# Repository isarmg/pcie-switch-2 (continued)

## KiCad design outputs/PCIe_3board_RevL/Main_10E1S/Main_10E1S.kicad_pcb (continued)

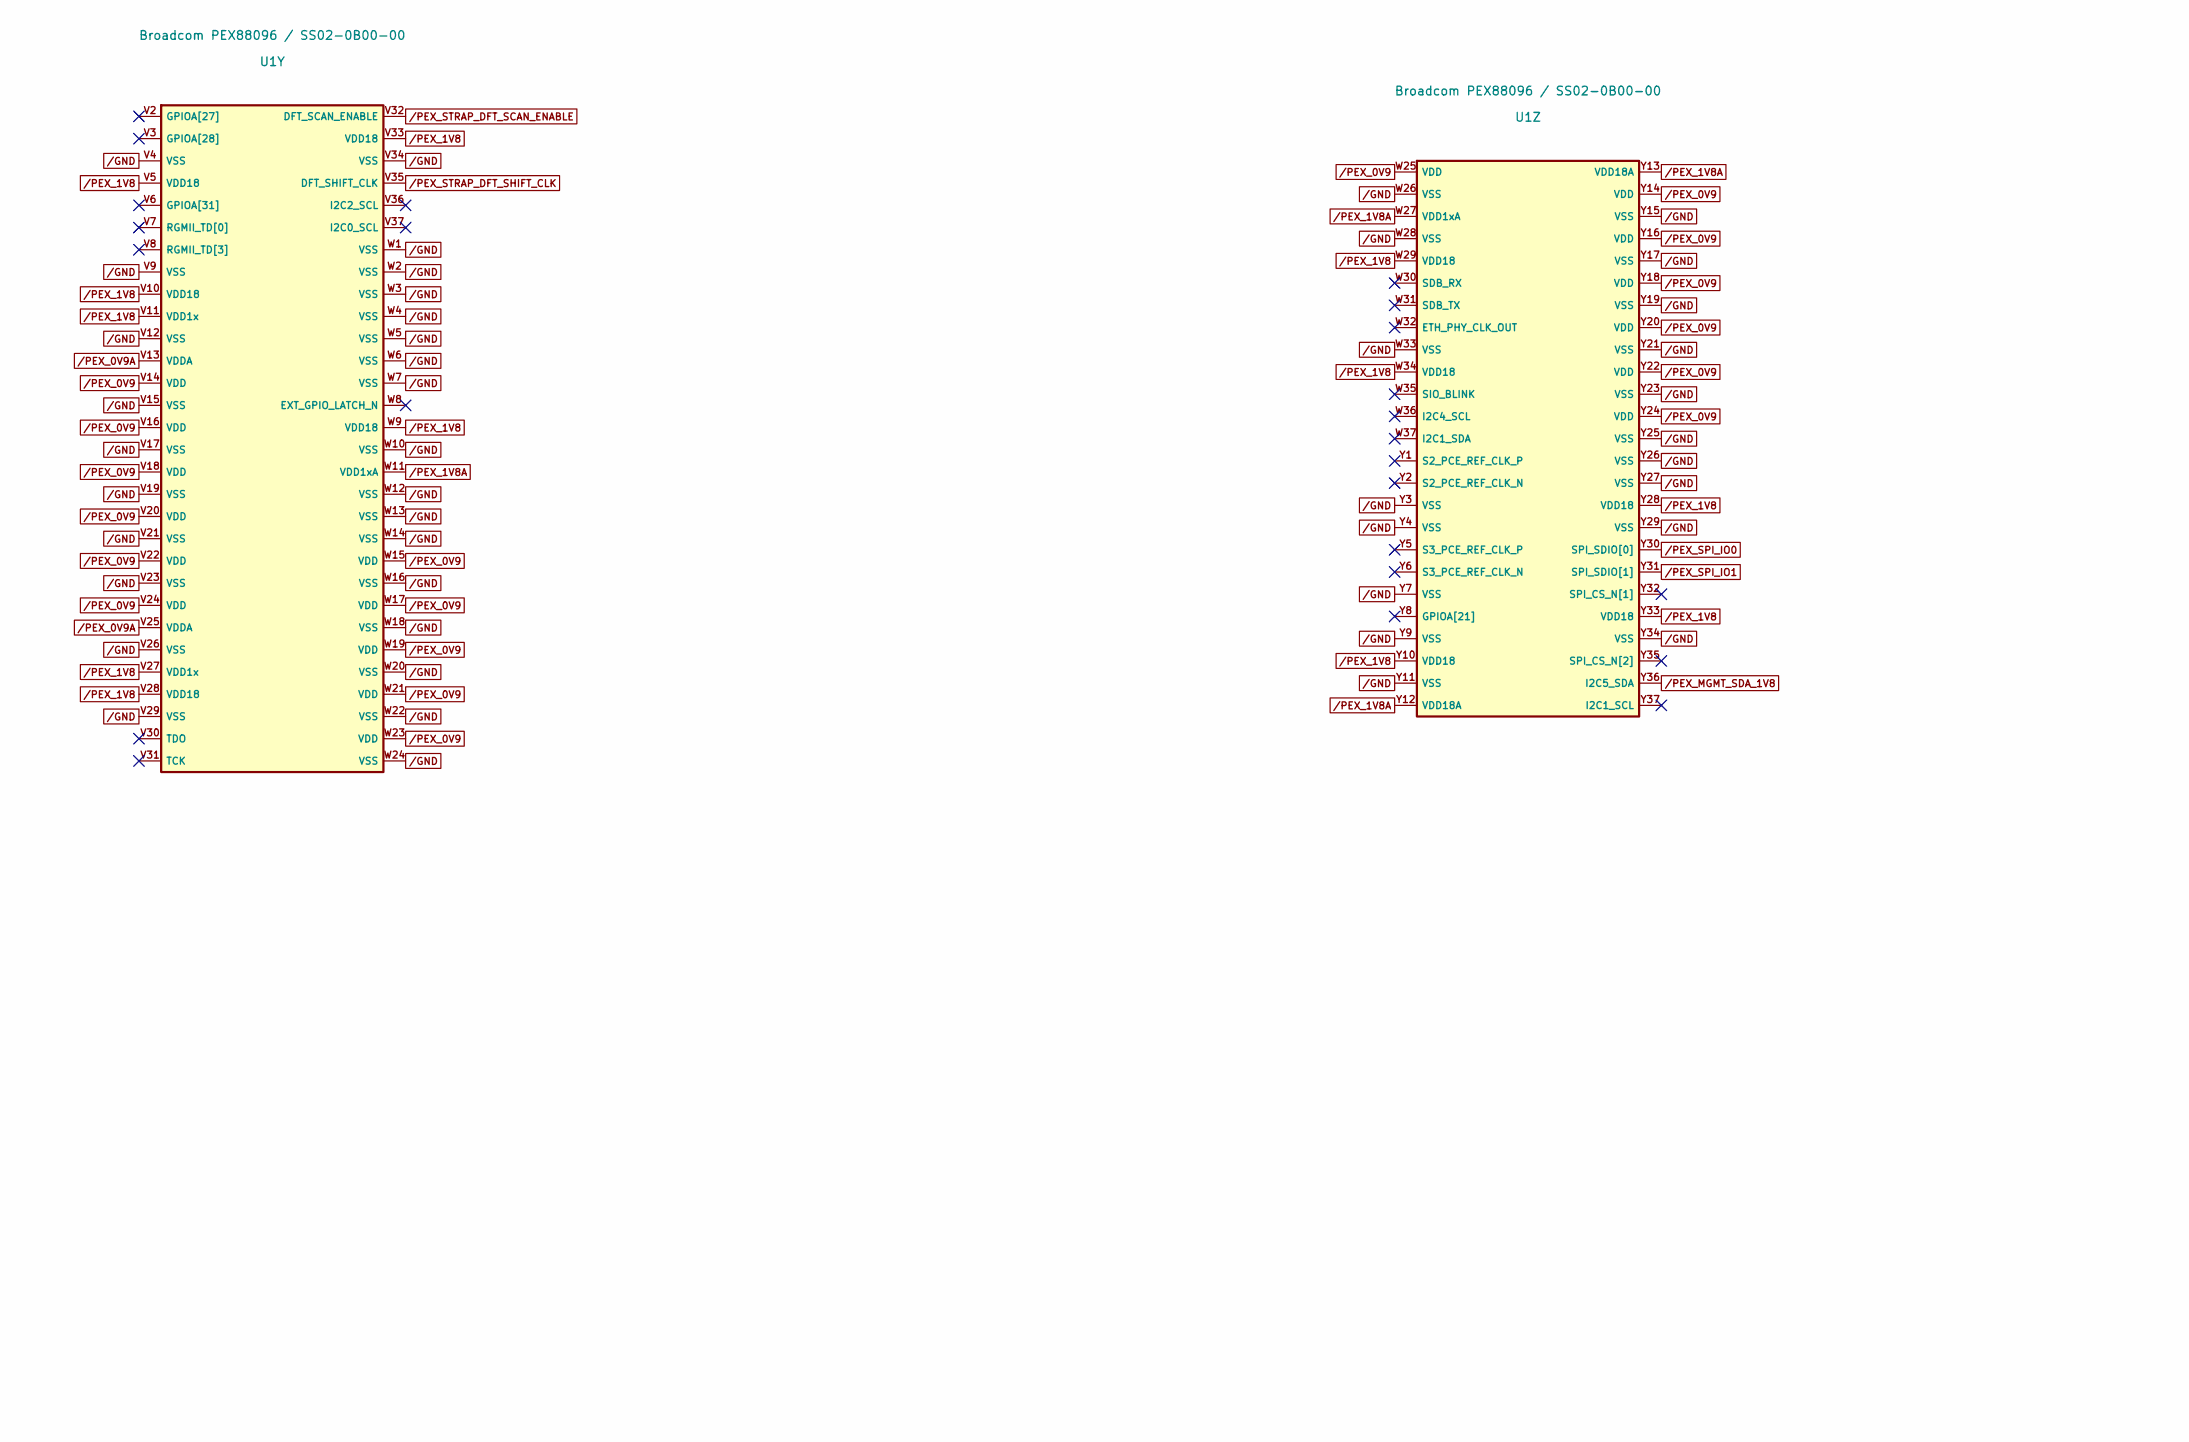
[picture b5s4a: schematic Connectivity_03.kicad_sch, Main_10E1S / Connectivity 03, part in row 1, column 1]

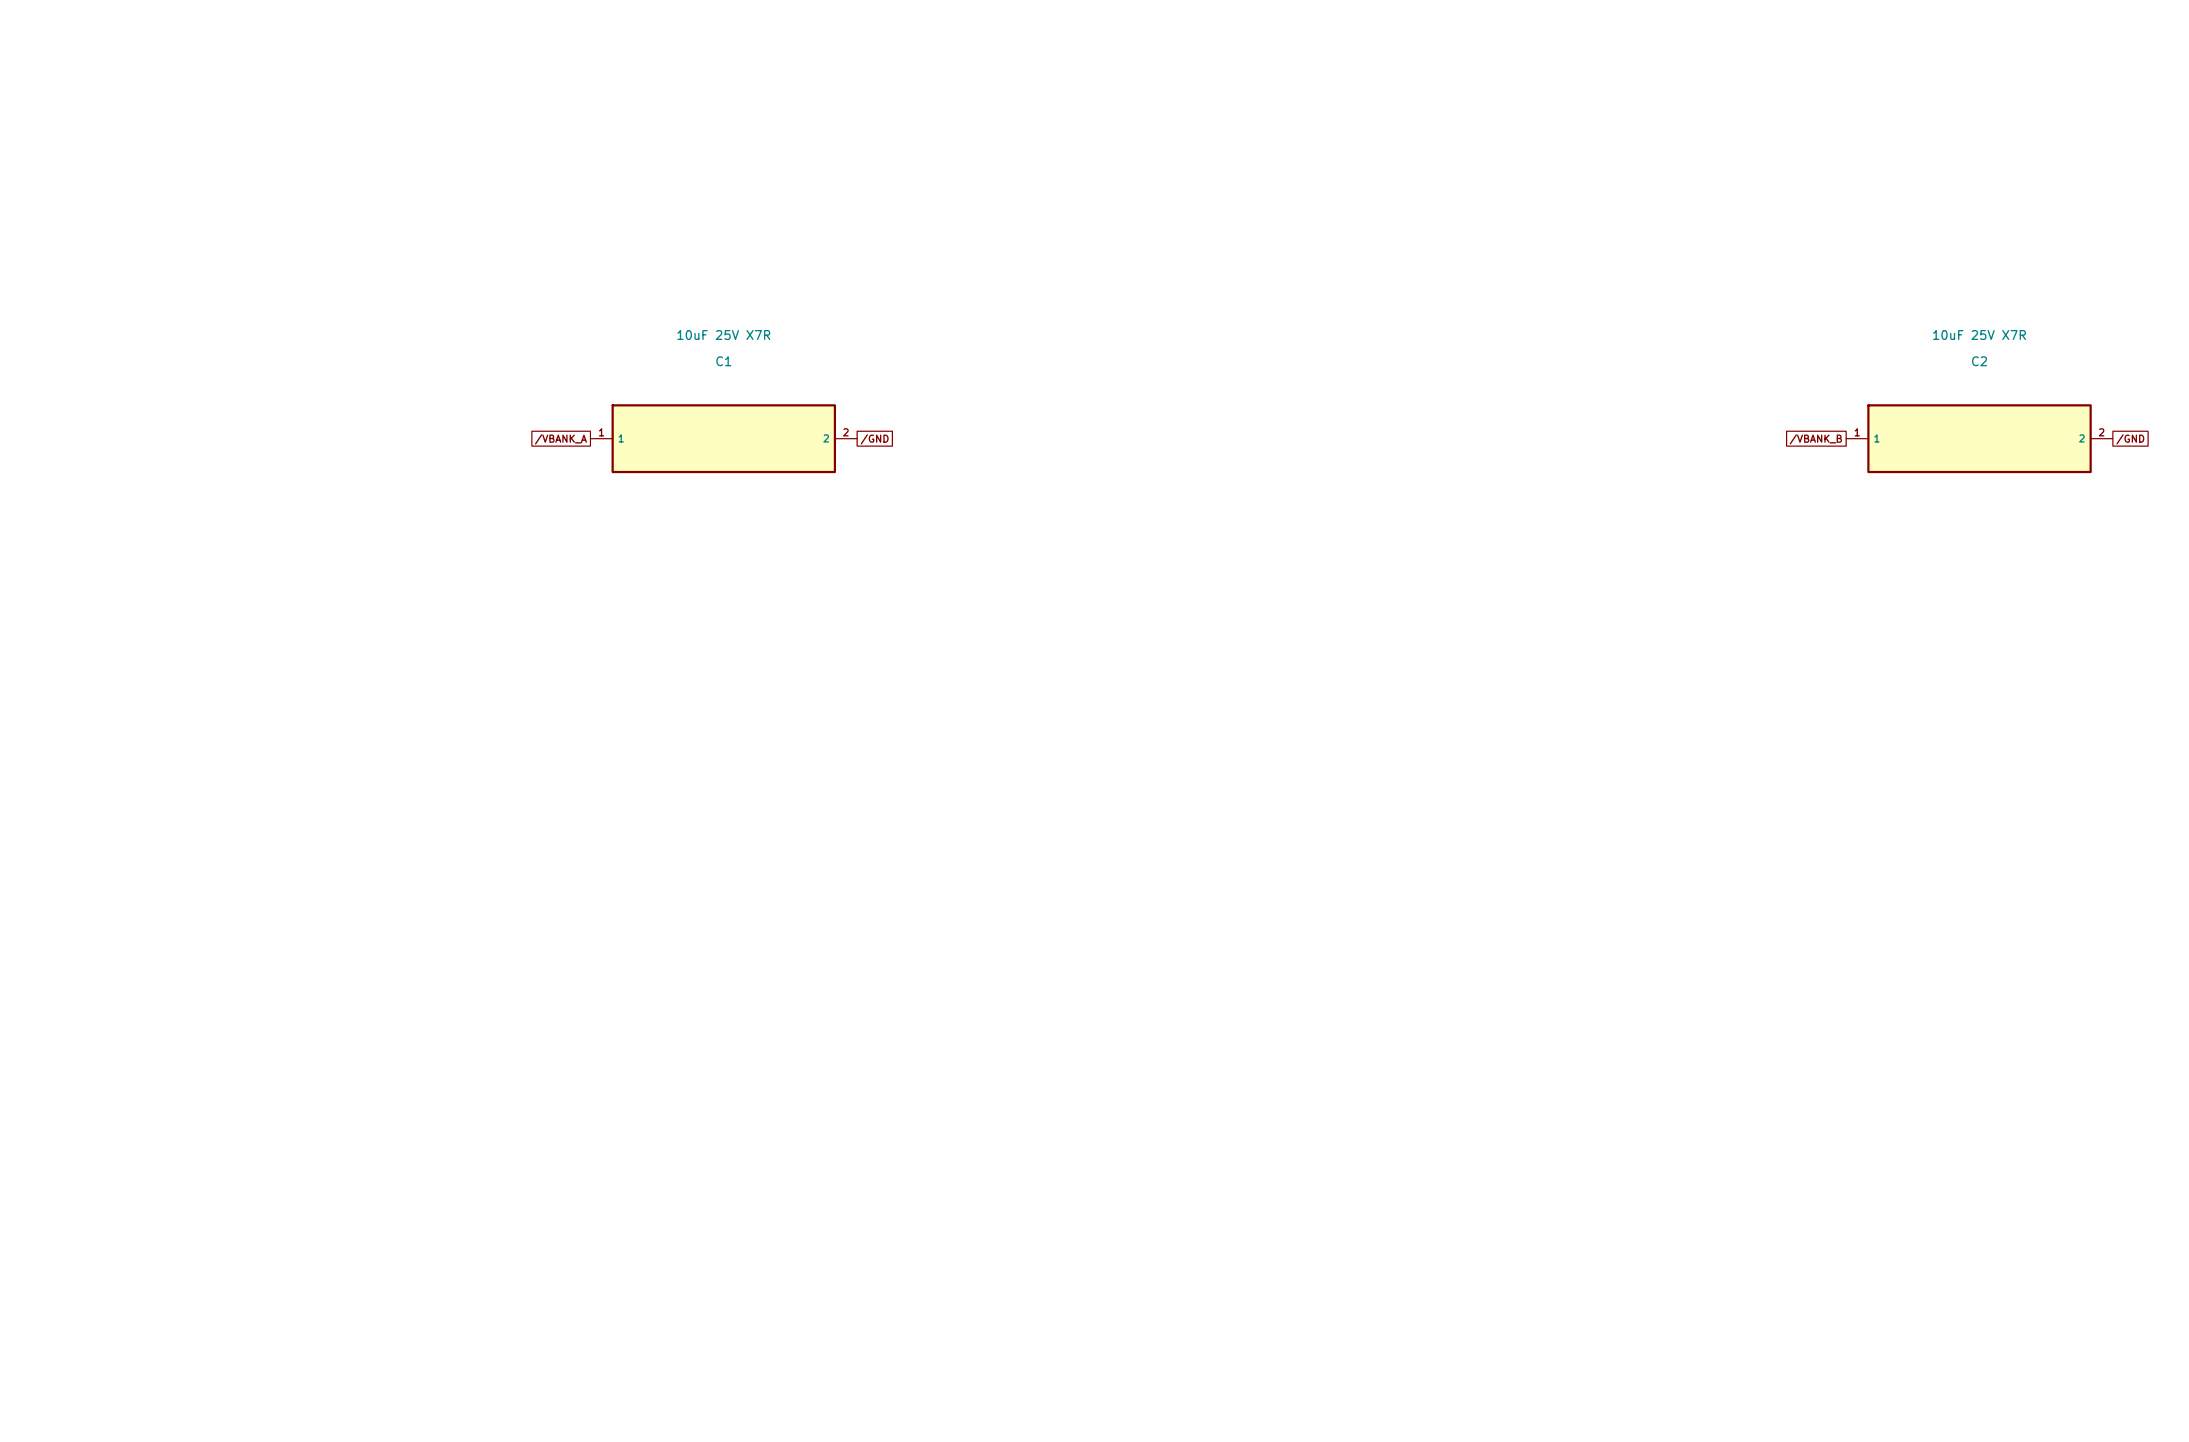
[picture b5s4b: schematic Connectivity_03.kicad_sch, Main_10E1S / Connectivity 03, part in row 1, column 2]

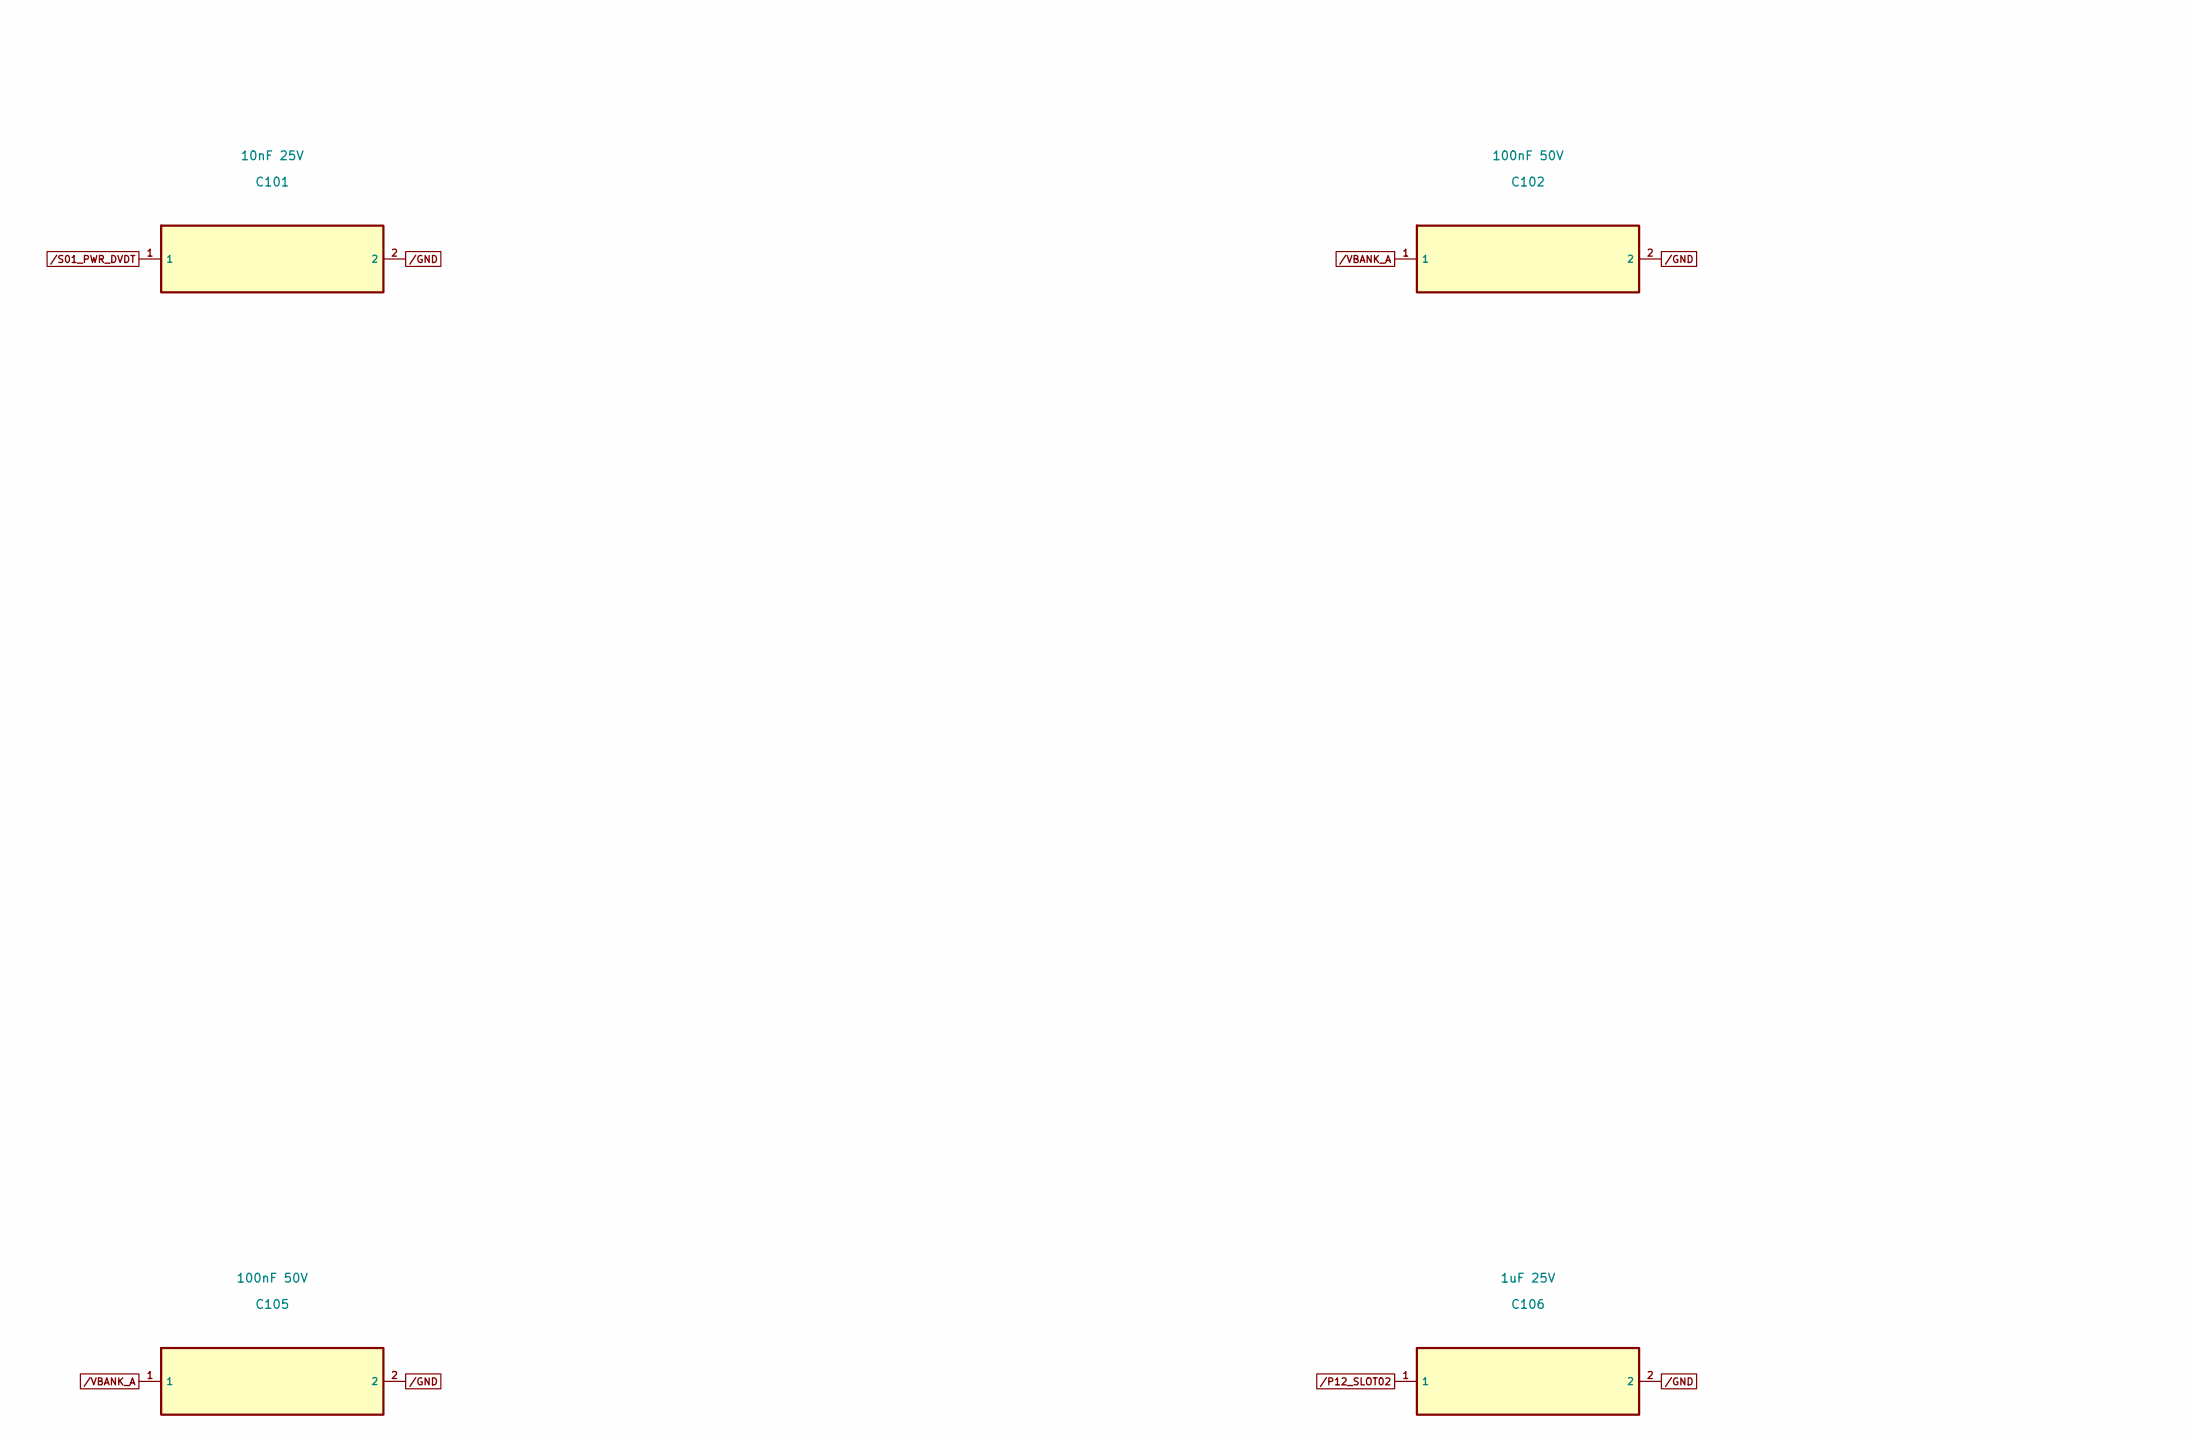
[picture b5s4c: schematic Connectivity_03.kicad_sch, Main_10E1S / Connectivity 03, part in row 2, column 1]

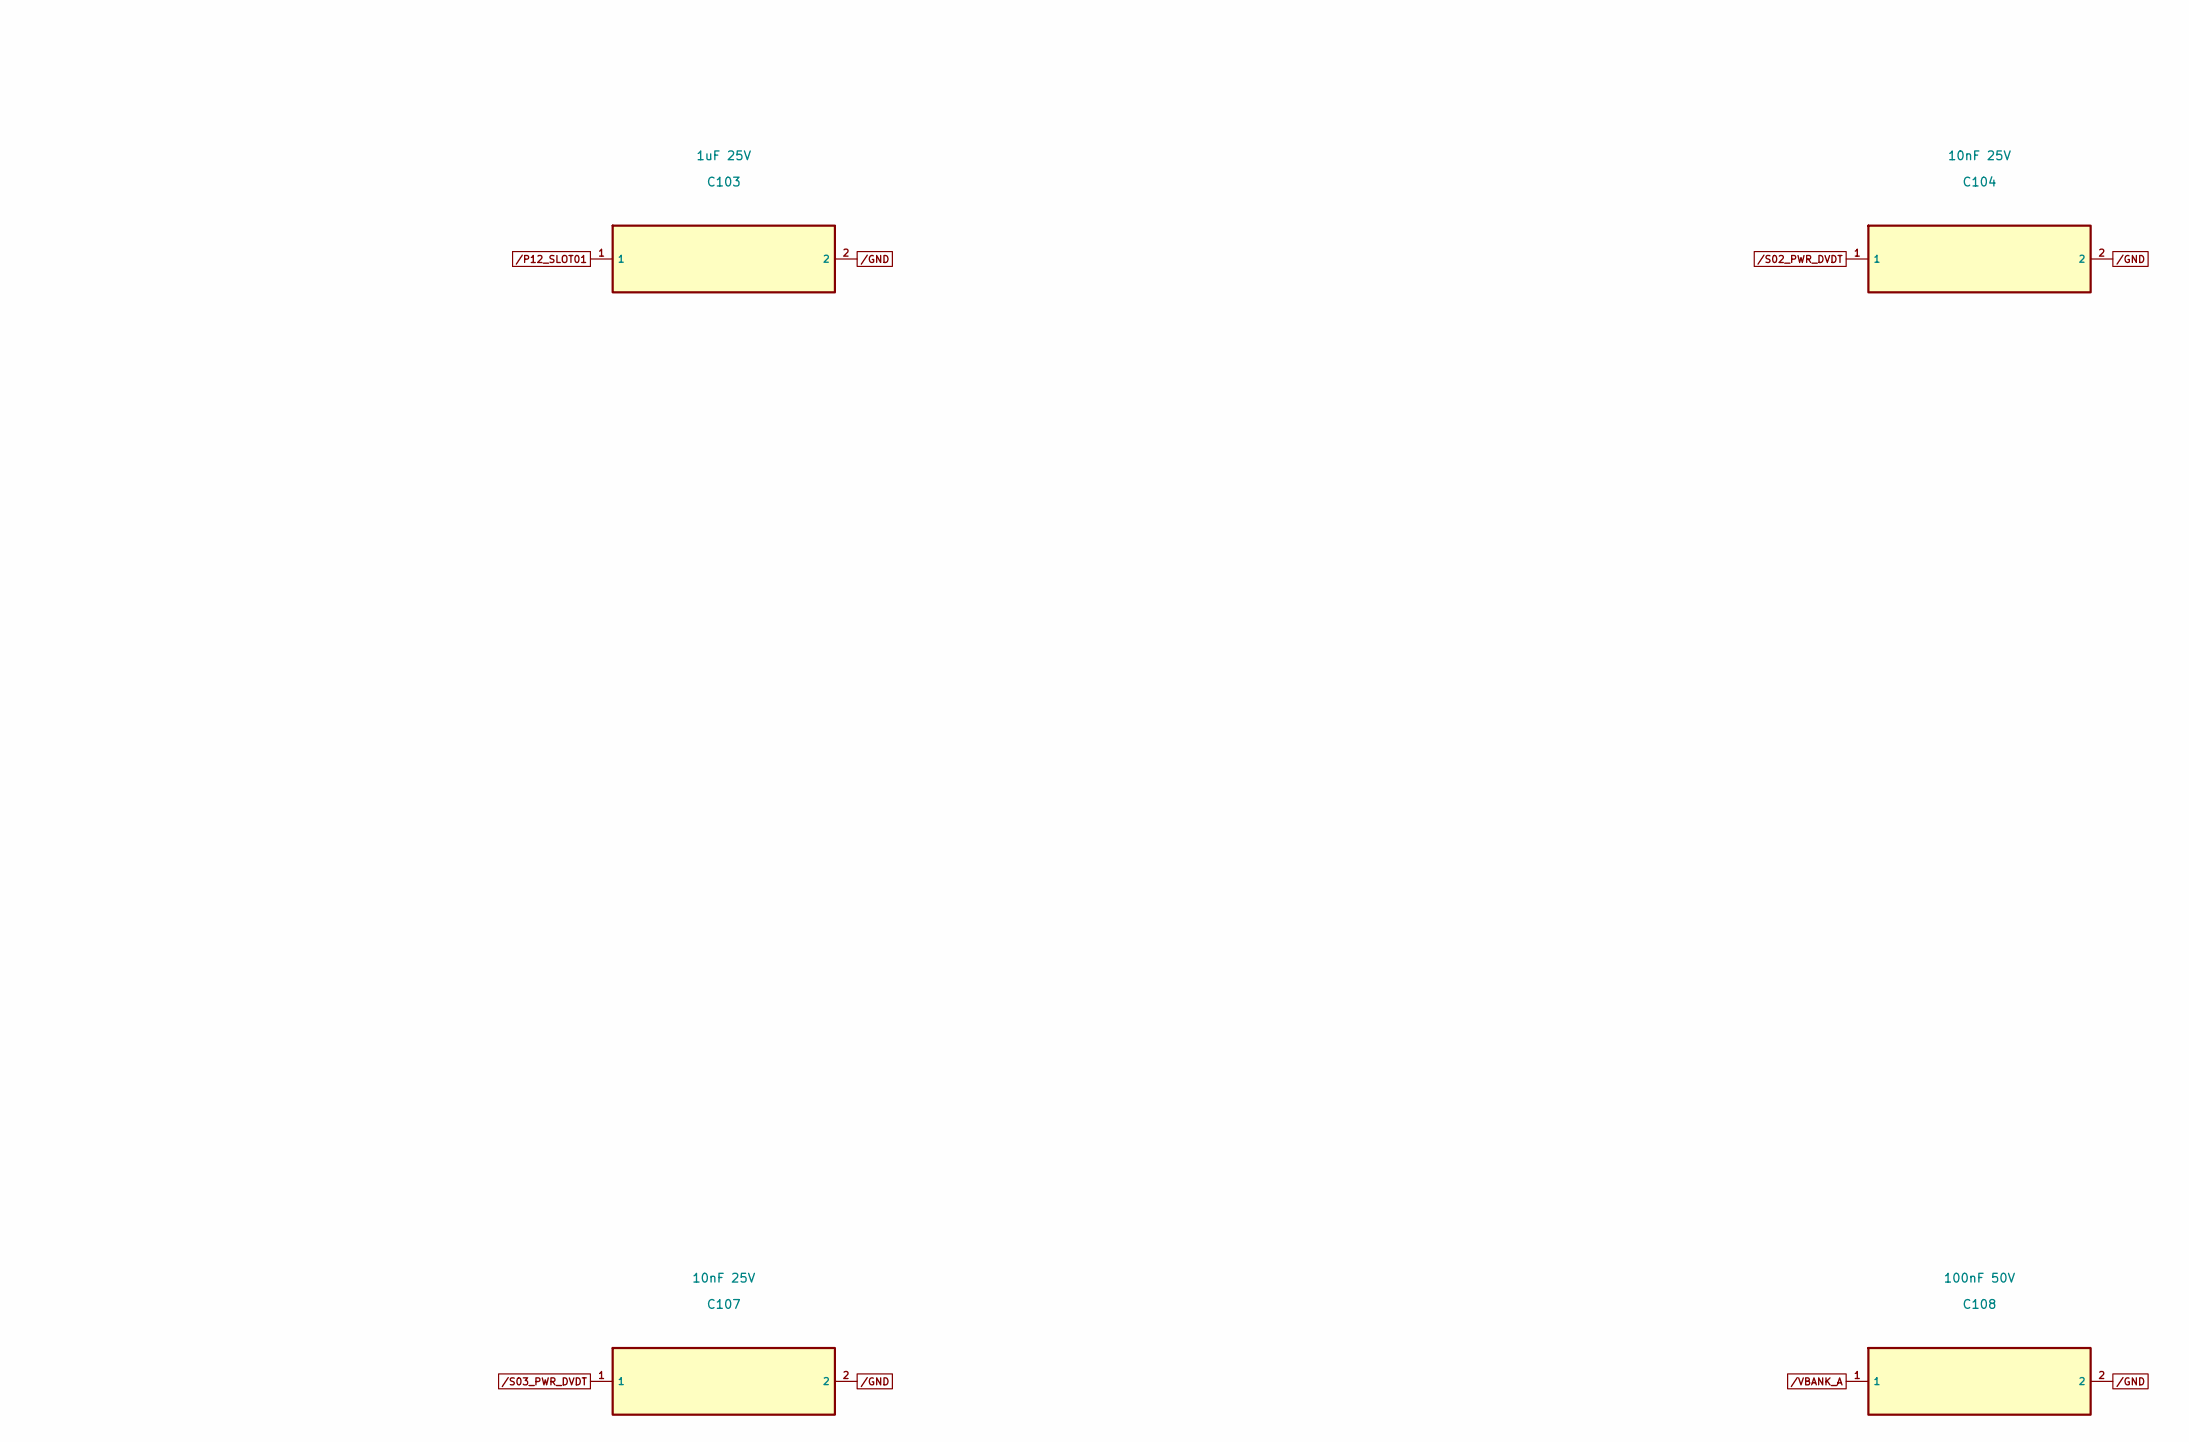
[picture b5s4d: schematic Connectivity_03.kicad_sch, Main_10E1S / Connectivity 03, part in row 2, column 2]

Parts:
C1, C2: 10uF 25V X7R; C_1210_3225Metric
C101, C104, C107: 10nF 25V; C_0402_1005Metric
C102, C105, C108: 100nF 50V; C_0603_1608Metric
C103, C106: 1uF 25V; C_0603_1608Metric
U1: Broadcom PEX88096 / SS02-0B00-00; Broadcom_PEX88096_BGA1550_37p5x42p5_1mm

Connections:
/GND: C1.2, C2.2, C101.2, C102.2, C103.2, C104.2, C105.2, C106.2, C107.2, C108.2, U1.V4 (VSS), U1.V9 (VSS), U1.V12 (VSS), U1.V15 (VSS), U1.V17 (VSS), U1.V19 (VSS), U1.V21 (VSS), U1.V23 (VSS), U1.V26 (VSS), U1.V29 (VSS), U1.V34 (VSS), U1.W1 (VSS), U1.W2 (VSS), U1.W3 (VSS), U1.W4 (VSS), U1.W5 (VSS), U1.W6 (VSS), U1.W7 (VSS), U1.W10 (VSS), U1.W12 (VSS), U1.W13 (VSS), U1.W14 (VSS), U1.W16 (VSS), U1.W18 (VSS), U1.W20 (VSS), U1.W22 (VSS), U1.W24 (VSS), U1.W26 (VSS), U1.W28 (VSS), U1.W33 (VSS), U1.Y3 (VSS), U1.Y4 (VSS), U1.Y7 (VSS), U1.Y9 (VSS), U1.Y11 (VSS), U1.Y15 (VSS), U1.Y17 (VSS), U1.Y19 (VSS), U1.Y21 (VSS), U1.Y23 (VSS), U1.Y25 (VSS), U1.Y26 (VSS), U1.Y27 (VSS), U1.Y29 (VSS), U1.Y34 (VSS); also elsewhere on the board
/P12_SLOT01: C103.1; also elsewhere on the board
/P12_SLOT02: C106.1; also elsewhere on the board
/PEX_0V9: U1.V14 (VDD), U1.V16 (VDD), U1.V18 (VDD), U1.V20 (VDD), U1.V22 (VDD), U1.V24 (VDD), U1.W15 (VDD), U1.W17 (VDD), U1.W19 (VDD), U1.W21 (VDD), U1.W23 (VDD), U1.W25 (VDD), U1.Y14 (VDD), U1.Y16 (VDD), U1.Y18 (VDD), U1.Y20 (VDD), U1.Y22 (VDD), U1.Y24 (VDD); also elsewhere on the board
/PEX_0V9A: U1.V13 (VDDA), U1.V25 (VDDA); also elsewhere on the board
/PEX_1V8: U1.V5 (VDD18), U1.V10 (VDD18), U1.V11 (VDD1x), U1.V27 (VDD1x), U1.V28 (VDD18), U1.V33 (VDD18), U1.W9 (VDD18), U1.W29 (VDD18), U1.W34 (VDD18), U1.Y10 (VDD18), U1.Y28 (VDD18), U1.Y33 (VDD18); also elsewhere on the board
/PEX_1V8A: U1.W11 (VDD1xA), U1.W27 (VDD1xA), U1.Y12 (VDD18A), U1.Y13 (VDD18A); also elsewhere on the board
/PEX_MGMT_SDA_1V8: U1.Y36 (I2C5_SDA)
/PEX_SPI_IO0: U1.Y30 (SPI_SDIO[0]); also elsewhere on the board
/PEX_SPI_IO1: U1.Y31 (SPI_SDIO[1]); also elsewhere on the board
/PEX_STRAP_DFT_SCAN_ENABLE: U1.V32 (DFT_SCAN_ENABLE)
/PEX_STRAP_DFT_SHIFT_CLK: U1.V35 (DFT_SHIFT_CLK)
/S01_PWR_DVDT: C101.1; also elsewhere on the board
/S02_PWR_DVDT: C104.1; also elsewhere on the board
/S03_PWR_DVDT: C107.1; also elsewhere on the board
/VBANK_A: C1.1, C102.1, C105.1, C108.1; also elsewhere on the board
/VBANK_B: C2.1; also elsewhere on the board
